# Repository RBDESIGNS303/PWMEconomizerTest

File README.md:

# PWMEconomizerTest

This is a work-in-progress to develop a board that can be used as an economizer for two contactors commonly used in EV conversions. It is not yet functional or ready for use.

Currently being discussed on the OpenInverter forum: https://openinverter.org/forum/viewtopic.php?t=3636

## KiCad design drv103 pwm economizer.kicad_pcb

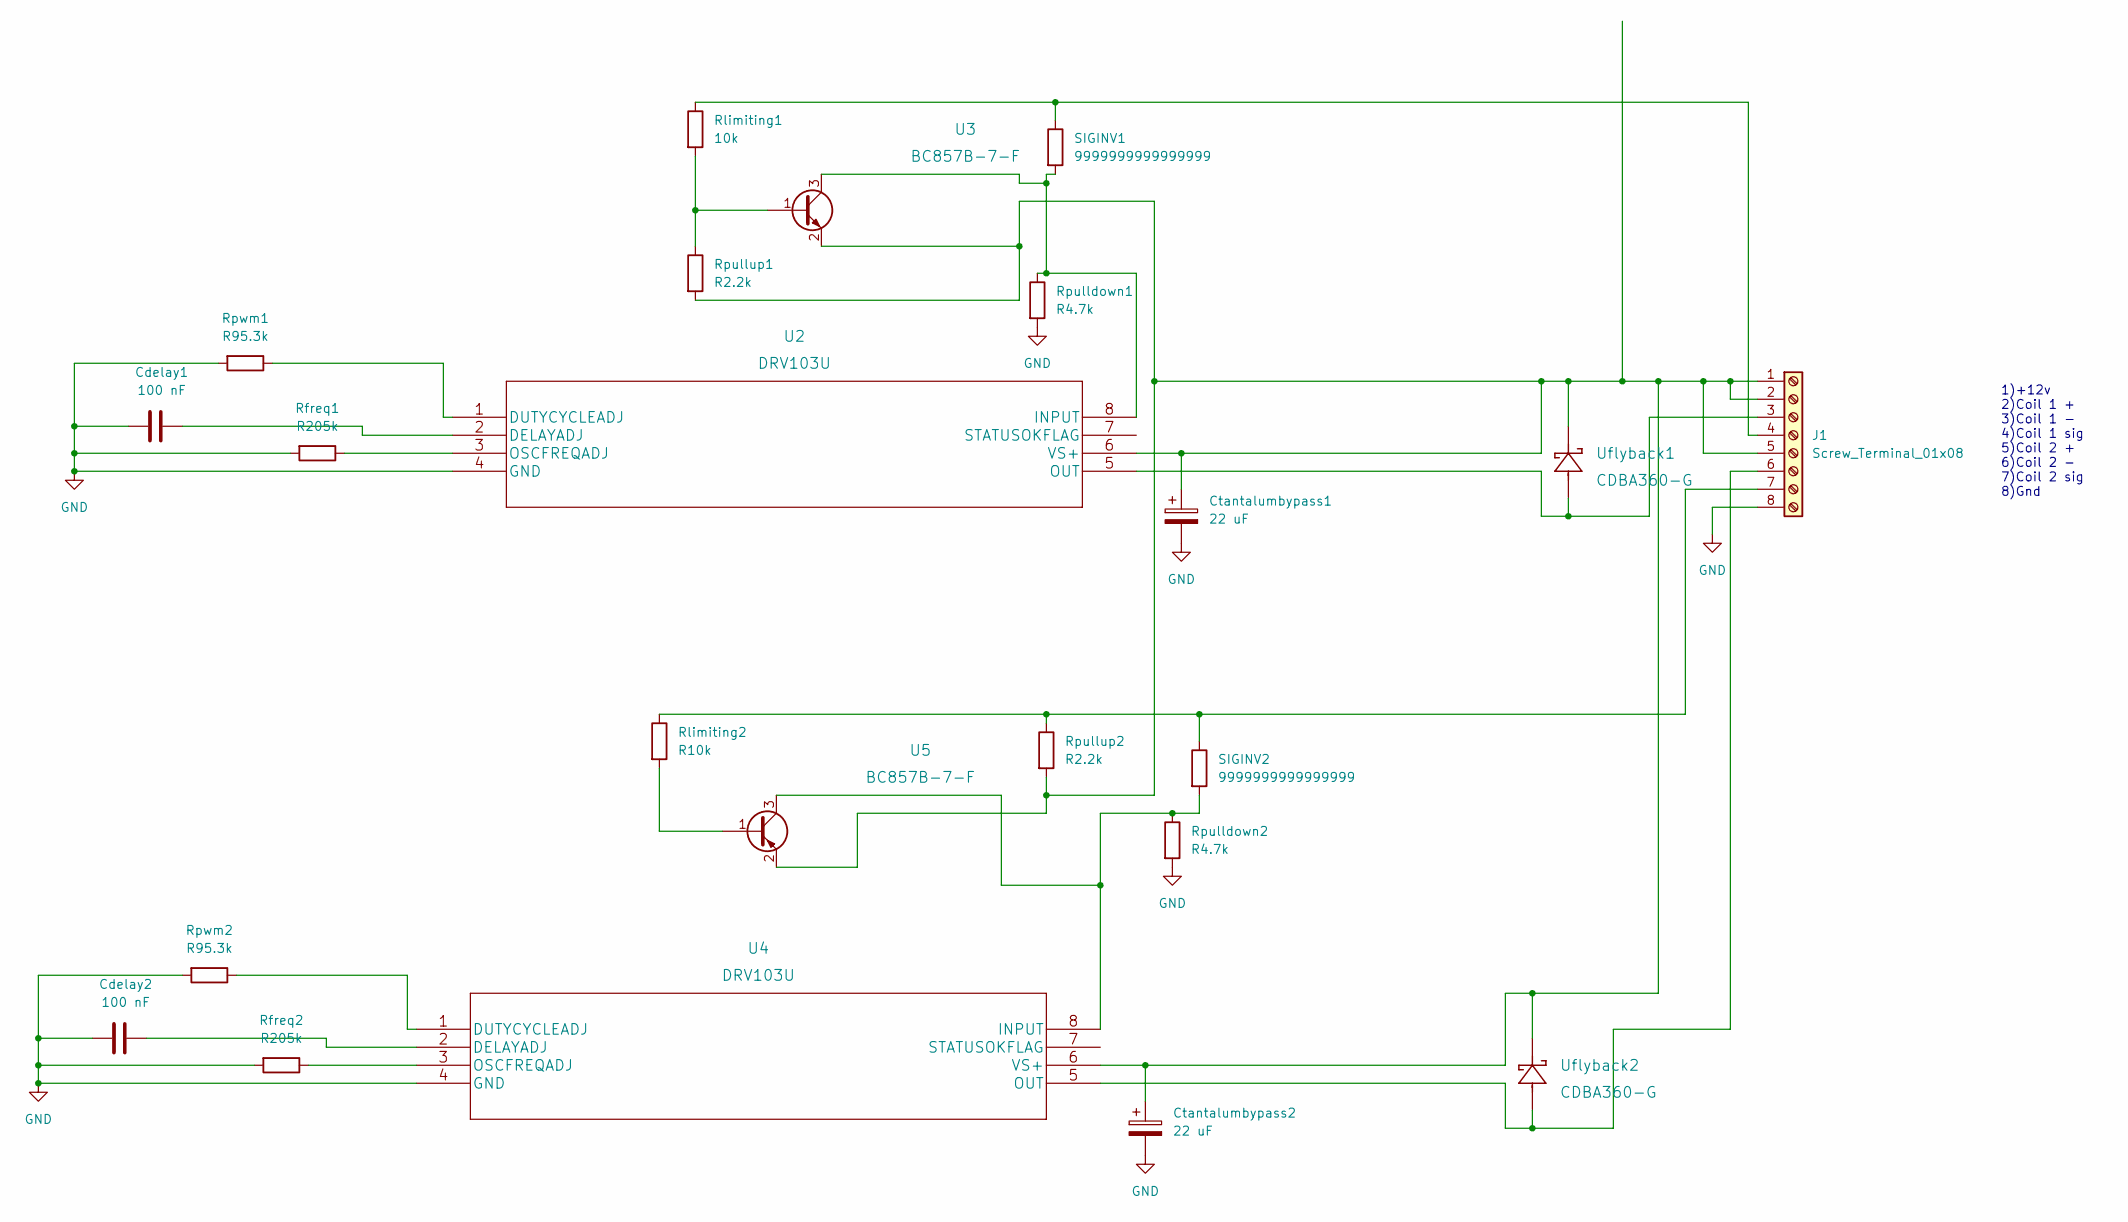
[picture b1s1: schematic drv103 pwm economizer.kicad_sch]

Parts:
Cdelay1, Cdelay2: 100 nF; C_1206_3216Metric_Pad1.33x1.80mm_HandSolder
Ctantalumbypass1, Ctantalumbypass2: 22 uF; C_1206_3216Metric_Pad1.33x1.80mm_HandSolder
J1: Screw_Terminal_01x08; TerminalBlock_Phoenix_PT-1,5-8-3.5-H_1x08_P3.50mm_Horizontal
Rfreq1, Rfreq2: R205k; R_1206_3216Metric_Pad1.30x1.75mm_HandSolder
Rlimiting1: 10k; R_1206_3216Metric_Pad1.30x1.75mm_HandSolder
Rlimiting2: R10k; R_1206_3216Metric_Pad1.30x1.75mm_HandSolder
Rpulldown1, Rpulldown2: R4.7k; R_1206_3216Metric_Pad1.30x1.75mm_HandSolder
Rpullup1, Rpullup2: R2.2k; R_1206_3216Metric_Pad1.30x1.75mm_HandSolder
Rpwm1, Rpwm2: R95.3k; R_1206_3216Metric_Pad1.30x1.75mm_HandSolder
SIGINV1, SIGINV2: 9999999999999999; R_1206_3216Metric_Pad1.30x1.75mm_HandSolder
U2, U4: DRV103U
U3, U5: BC857B-7-F; SOT-23
Uflyback1, Uflyback2: CDBA360-G

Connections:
GND: Cdelay1.2, Cdelay2.2, Ctantalumbypass1.2, Ctantalumbypass2.2, J1.8, Rfreq1.2, Rfreq2.2, Rpulldown1.2, Rpulldown2.2, Rpwm1.2, Rpwm2.2, U2.4 (GND), U4.4 (GND)
unnamed: Cdelay1.1, U2.2 (DELAYADJ)
unnamed: Cdelay2.1, U4.2 (DELAYADJ)
unnamed: Ctantalumbypass1.1, Ctantalumbypass2.1, J1.1, J1.2, J1.5, Rpullup1.2, Rpullup2.2, U2.6 (VS+), U3.2 (E), U4.6 (VS+), U5.2 (E), Uflyback1.1, Uflyback2.1
unnamed: J1.3, U2.5 (OUT), Uflyback1.2
unnamed: J1.4, Rlimiting1.1, SIGINV1.1
unnamed: J1.6, U4.5 (OUT), Uflyback2.2
unnamed: J1.7, Rlimiting2.1, Rpullup2.1, SIGINV2.1
unnamed: Rfreq1.1, U2.3 (OSCFREQADJ)
unnamed: Rfreq2.1, U4.3 (OSCFREQADJ)
unnamed: Rlimiting2.2, U5.1 (B)
unnamed: Rpulldown2.1, SIGINV2.2, U4.8 (INPUT), U5.3 (C)
unnamed: Rpwm1.1, U2.1 (DUTYCYCLEADJ)
unnamed: Rpwm2.1, U4.1 (DUTYCYCLEADJ)
unnamed: Rpulldown1.1, SIGINV1.2, U2.8 (INPUT), U3.3 (C)
unnamed: Rlimiting1.2, Rpullup1.1, U3.1 (B)

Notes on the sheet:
1)+12v 2)Coil 1 + 3)Coil 1 - 4)Coil 1 sig 5)Coil 2 + 6)Coil 2 - 7)Coil 2 sig 8)Gnd

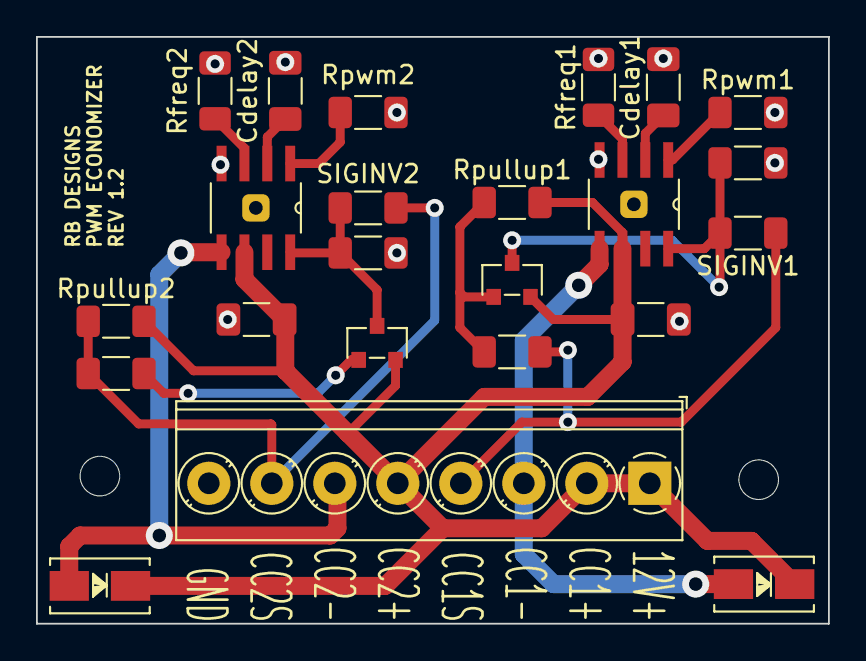
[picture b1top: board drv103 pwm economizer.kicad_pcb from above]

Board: 2 copper layers, 44.0 x 32.6 mm, 23 parts (0 on the bottom side), 16 nets.

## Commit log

2023-05-28 Add files via upload
    Current status of project. Transistors need a complete rework.

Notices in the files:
parts and their libraries:
Copyright 2021 Accelerated Designs. All rights reserved.
